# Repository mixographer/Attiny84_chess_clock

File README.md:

# Attiny84 Chess Clock
A chess clock based on the Atmel Attiny84 micorcontroller.

This project is a simple chess clock based on the Atmel Attiny84 micoprocessor. It uses the SCD55104 LED Display 
module to display player times and user interface menus. The time periods are adjustable and the clock operated 
in three different modes. 

# Modes
## Sudden Death
In Sudden-death mode, your clock runs when it is your turn, and you lose when you run out of time. 

## Fischer Increment
In Fischer Increment mode, an increment is added at the start of each turn. In Fischer Increment mode you can actually 
add time to your total if you move faster than the increment amount. 

## Hourglass
In Hourglass mode, as one player's time goes down, the other player's time goes up. 

# Operation 
The Chess Clock has four buttons that are used during gameplay, and to set the parameters of the clock. 
1. Start/Reset
2. Player 1/Down
3. Player 2/Up
4. Pause/Enter

## Start
To begin using the clock press the Start/Reset button. 

## Set Time
You will be prompted to set the time period for the game with the text "Set Time:" Use the 'Player 1/Down' and 'Player 2/Up' buttons to set the time period. The default time is 2 minutes. The 'down' button reduces the time period while the 'up' button adds time. If the current time setting is 1:00 the down button will reduce the time period by 50%. The 'up' button adds 1 minute to the time period. 

When you have set the desired time period with the 'down' and 'up' buttons, press the 'Pause/Enter' button to accept the time period. 

## Set Mode
You will be prompted to set the mode of the clock.

#### Sudden Death
The default mode is Sudden Death or Guillotine. If you would like this mode simply hit the "Pause/Enter" button. 
The time period will be displayed for both players, and a play can begin. You can also scroll through the all modes with the 'Player 1/Down' and Player 2/Up' buttons. 

#### Fischer Increment
Fischer increment mode can be selected by pressing the 'Player 1/Down' or 'Player2/Up button at the 'Set Mode' prompt. When 'Fischer' is displayed on the clock you can accept Fischer delay mode by pressing the 'Pause/Enter' button. 

Set the increment. 
In Fischer increment mode, an increment period is required. The clock will prompt for the increment with the display "Inc?: 0:05." Set the desired increment with the 'Player 1/Down' and 'Player 2/Up' buttons. The increment adjusts in 1 second increments. Accept the increment with the 'Pause/Enter' button, the time period will be displayed and play can begin.

#### Hourglass
Hourglass mode can be selected by pressing the 'Player 1/Down' or 'Player2/Up' button at the 'Set Mode' prompt. Hourglass mode operates like an hourglass. As time is decreasing for one player, it is increasing for the other player. Once 'Hourglass' is displayed, press the 'Pause/Enter' button and play can begin. 

## Play
Once the time period and mode have been set, the clock is ready to use. When time runs out for a player and indicator light will illuminate and the word "FLAG" will appear for the player who ran out of time. After a short period of time the clock will shut down. To start a new game, press the 'Start/Reset' button. 

If during play, the clock needs to be paused for any reason, the 'Pause/Enter' will stop the clock at the current time. Play may be restarted by pressing either the 'Player1' or 'Player 2' button. Do not leave the clock paused for extended periods of time as that will prevent the clock from powering down and will drain the batteries. 

###Keywords
Chess Clock, DIY Chess Clock, Atmel, Attiny, Blitz, Bullet, Chess.

- - - 
### License
Licensed under the MIT License. See LICENSE.txt.

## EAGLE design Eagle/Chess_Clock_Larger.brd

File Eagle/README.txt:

I have tested 'scd55104_chess_clock.brd' and it works fine. I have not yet received 'Chess_Clock_Larger.brd' back from the board house, so I don't know if it works.

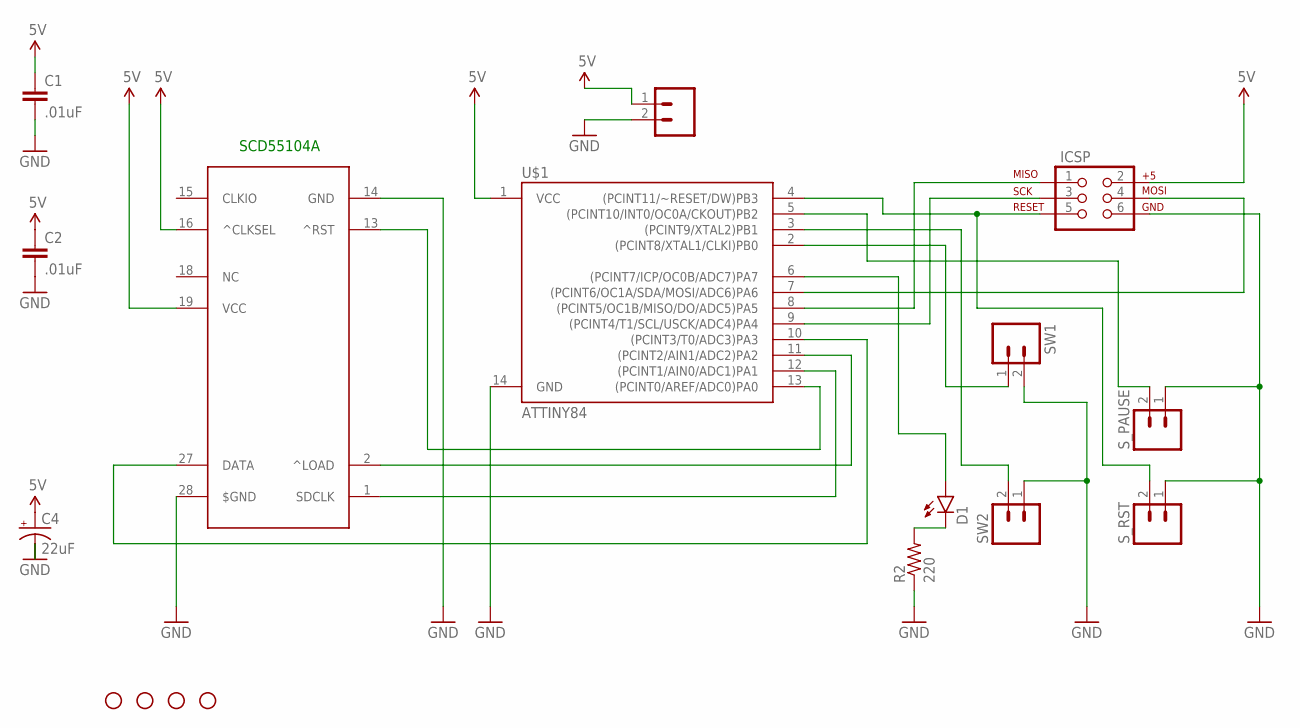
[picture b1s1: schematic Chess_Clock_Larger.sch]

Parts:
C1, C2: .01uF; CAP-PTH-SMALL
C4: 22uF; CPOL-RADIAL-10UF-25V
D1: LED5MM
ICSP: AVR_SPI_PRG_6PTH; 2X3
R2: 220; 1206
SCD55104A: SCD_55104A; SCD55104A
STANDOFF1, STANDOFF2, STANDOFF3, STANDOFF4: STAND-OFF
SW1, SW2, SW3: M02PTH; 1X02
S_PAUSE: M02PTH; 1X02
S_RST: M02PTH; 1X02
U$1: ATTINY84; SO14

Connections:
5V: C1.1, C2.1, C4.1 (+), ICSP.2, SCD55104A.16 (^CLKSEL), SCD55104A.19 (VCC), SW3.1, U$1.1 (VCC)
GND: C1.2, C2.2, C4.2 (-), ICSP.6, R2.1, SCD55104A.14 (GND), SCD55104A.28 ($GND), SW1.2, SW2.1, SW3.2, S_PAUSE.1, S_RST.1, U$1.14 (GND)
unnamed: D1.K (C), R2.2
unnamed: SCD55104A.13 (^RST), U$1.13 ((PCINT0/AREF/ADC0)PA0)
unnamed: ICSP.4, U$1.7 ((PCINT6/OC1A/SDA/MOSI/ADC6)PA6)
unnamed: ICSP.5, S_RST.2, U$1.4 ((PCINT11/~RESET/DW)PB3)
unnamed: ICSP.1, U$1.8 ((PCINT5/OC1B/MISO/DO/ADC5)PA5)
unnamed: ICSP.3, U$1.9 ((PCINT4/T1/SCL/USCK/ADC4)PA4)
unnamed: SCD55104A.1 (SDCLK), U$1.12 ((PCINT1/AIN0/ADC1)PA1)
unnamed: SCD55104A.2 (^LOAD), U$1.11 ((PCINT2/AIN1/ADC2)PA2)
unnamed: SW1.1, U$1.2 ((PCINT8/XTAL1/CLKI)PB0)
unnamed: SW2.2, U$1.3 ((PCINT9/XTAL2)PB1)
unnamed: S_PAUSE.2, U$1.5 ((PCINT10/INT0/OC0A/CKOUT)PB2)
unnamed: D1.A, U$1.6 ((PCINT7/ICP/OC0B/ADC7)PA7)
unnamed: SCD55104A.27 (DATA), U$1.10 ((PCINT3/T0/ADC3)PA3)

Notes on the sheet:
SCD55104A

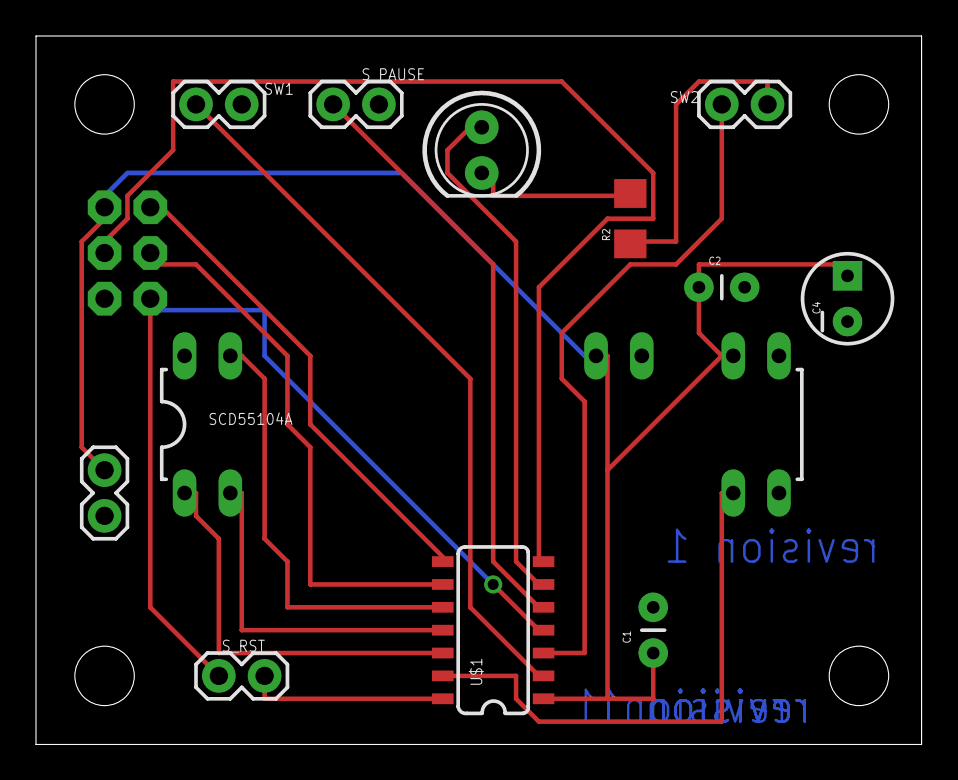
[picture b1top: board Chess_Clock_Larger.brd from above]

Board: 2 copper layers, 49.2 x 39.4 mm, 17 parts (1 on the bottom side), 15 nets.

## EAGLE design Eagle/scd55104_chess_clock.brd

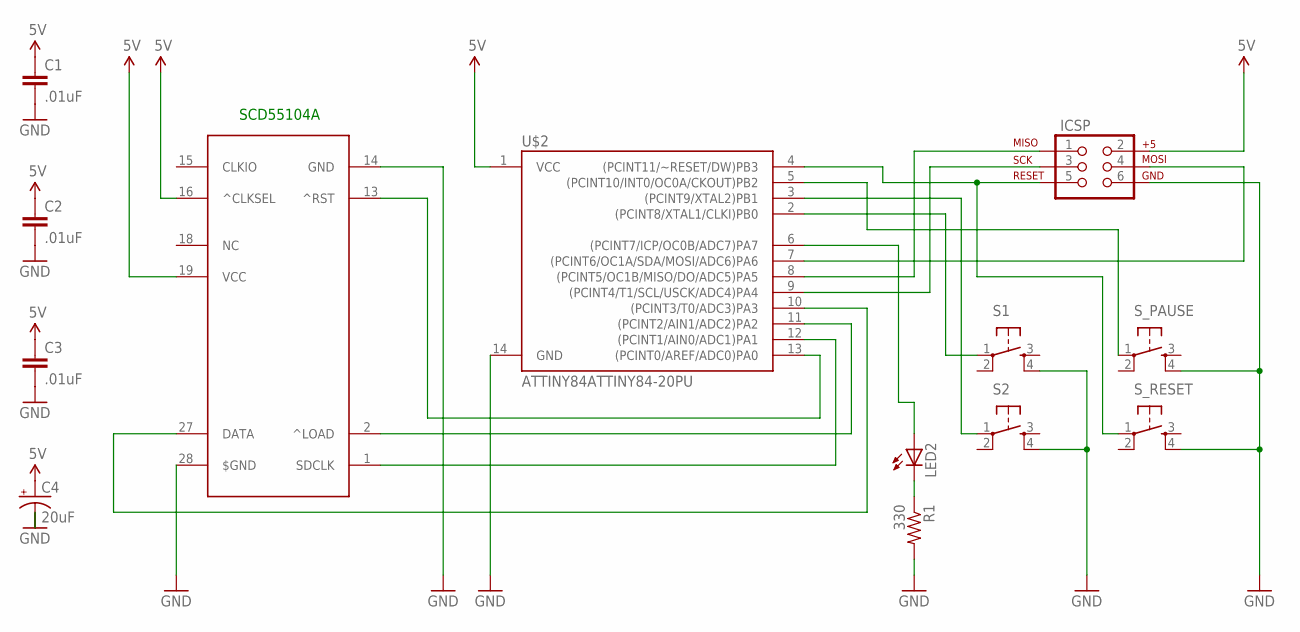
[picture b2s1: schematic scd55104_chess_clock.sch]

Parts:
C1, C2, C3: .01uF; CAP-PTH-SMALL
C4: 20uF; CPOL-RADIAL-10UF-25V
ICSP: AVR_SPI_PRG_6PTH; 2X3
LED2: LED3MM
R1: 330; AXIAL-0.4
S1, S2: TAC_SWITCHPTH; TACTILE-PTH
SCD55104A: SCD_55104A; SCD55104A
S_PAUSE: TAC_SWITCHPTH; TACTILE-PTH
S_RESET: TAC_SWITCHPTH; TACTILE-PTH
U$2: ATTINY84ATTINY84-20PU; DIL14

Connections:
5V: C1.1, C2.1, C3.1, C4.1 (+), ICSP.2, SCD55104A.16 (^CLKSEL), SCD55104A.19 (VCC), U$2.1 (VCC)
GND: C1.2, C2.2, C3.2, C4.2 (-), ICSP.6, R1.P$2 (2), S1.4, S2.4, SCD55104A.14 (GND), SCD55104A.28 ($GND), S_PAUSE.4, S_RESET.4, U$2.14 (GND)
unnamed: SCD55104A.13 (^RST), U$2.13 ((PCINT0/AREF/ADC0)PA0)
unnamed: ICSP.4, U$2.7 ((PCINT6/OC1A/SDA/MOSI/ADC6)PA6)
unnamed: ICSP.5, S_RESET.1, U$2.4 ((PCINT11/~RESET/DW)PB3)
unnamed: ICSP.1, U$2.8 ((PCINT5/OC1B/MISO/DO/ADC5)PA5)
unnamed: ICSP.3, U$2.9 ((PCINT4/T1/SCL/USCK/ADC4)PA4)
unnamed: SCD55104A.1 (SDCLK), U$2.12 ((PCINT1/AIN0/ADC1)PA1)
unnamed: SCD55104A.2 (^LOAD), U$2.11 ((PCINT2/AIN1/ADC2)PA2)
unnamed: S1.1, U$2.2 ((PCINT8/XTAL1/CLKI)PB0)
unnamed: S2.1, U$2.3 ((PCINT9/XTAL2)PB1)
unnamed: LED2.K (C), R1.P$1 (1)
unnamed: S_PAUSE.1, U$2.5 ((PCINT10/INT0/OC0A/CKOUT)PB2)
unnamed: LED2.A, U$2.6 ((PCINT7/ICP/OC0B/ADC7)PA7)
unnamed: SCD55104A.27 (DATA), U$2.10 ((PCINT3/T0/ADC3)PA3)

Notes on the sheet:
SCD55104A

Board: 2 copper layers, 13 parts (0 on the bottom side), 15 nets, no tracks yet.

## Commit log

2015-02-28 Initial commit of the Arduino Sketch.
2015-03-01 adding directory for Eagle files
2015-03-01 deleted bad filename file
2015-03-02 Images of some prototype stages
2015-03-02 Adding Eagle files, including schematic and board file.
2015-03-02 Update README.md
    Adding Mode info to Readme.md
2015-03-02 Adding datasheet for scd55104A LED displays.
2015-03-02 Update README.md
    Formatting changes and adding keywords.
2015-03-02 Adding MIT License file.
2015-03-03 Update README.md
    Adding license text in README.md
2015-03-03 Update README.md
    Added usage instructions.
2015-03-03 Update README.md
    More usage info.
2015-03-03 Update README.md
    Fischer mode should be called increment not delay.
2015-03-03 Adding the svg file used to cut the enclosures.
2015-03-04 The correct file for the enclosure is box_final_3mm_revised.svg. This file should be cut out of 1/8" ply, as close to 3mm as possible.
2015-03-04 Adding README for the SVG files.
2015-03-04 Original Adobe Illustrator file.
2015-03-04 Adding an image of the first laser cut test enclosure.
2015-03-05 Added mounting holes to front panel
2015-03-05 changed the size of the LED hole, for an interference fit.
2015-03-06 adding a lager board for easier assembly.
2015-03-11 Adding images of the clock in the laser cut enclosure.
2015-03-11 added note about untested nature of the current drawings.
2015-03-11 modified warning note.
2015-03-11 Added readem.txt, noting I haven't tested with the larger board.
2015-03-12 User testing showed that the mode setting should be with Up/Down/Enter buttons, just like adding and subtracting time in setTime. I have changed it to that menu method.
    TODO: should make gameMode 2 into a real mode rather than just a default mode.
2015-03-12 Update README.md
    Changed the readme to reflect the new method of setting the game mode.
2015-03-12 Set GameMode to '2' so that gameMode -- actually means somthing. starting with gameMode undefined didn't work!
2015-03-12 cleanup of some comments
2015-03-12 cleaning up some unused junk.
2015-03-17 Adding in some de-bounce delays for the bouncy buttons I used.
2015-04-14 Had a bug in Fischer Mode where the time was always set to 2:00. Fixed.

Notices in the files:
parts and their libraries:
SparkFun-Connectors: Licensing: Creative Commons ShareAlike 4.0 International - https://creativecommons.org/licenses/by-sa/4.0
